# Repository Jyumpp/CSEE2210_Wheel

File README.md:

# CSEE2210_Wheel
## Rafferty Wong, Nick Piotrowski, Hunter Halloran

We made a wheelchair wheel with eddy-current braking

- Arduino code in `wheelSpeed.ino`
- Circuit schematic in `Wheel.sch`
- Circut board drawing in `Wheel.brd`
- Disk sketches in `image.png` and `image (1).png`
- Testing results in `csee graph.pdf`

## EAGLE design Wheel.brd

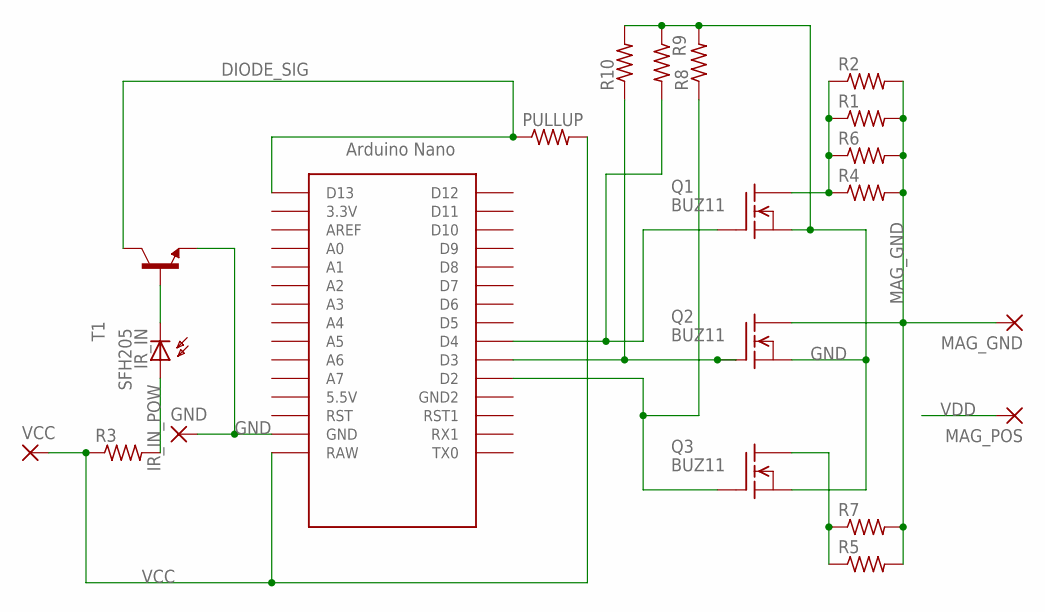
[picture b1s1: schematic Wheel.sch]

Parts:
GND: 3,81/1,4
IR_IN: SFH205
MAG_GND: 3,81/1,4
MAG_POS: 3,81/1,4
PULLUP: R-US_0204/7; 0204/7
Q1, Q2, Q3: BUZ11; TO220
R1, R2, R3, R4, R5, R6, R7, R8, R9, R10: R-US_0204/7; 0204/7
T1: -NPN-TO92-EBC; TO92-EBC
U$1: NANO
VCC: 3,81/1,4

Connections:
D2_SIG: Q3.1 (G), R8.1, U$1.D2
D3_SIG: Q2.1 (G), R10.1, U$1.D3
D4_SIG: Q1.1 (G), R9.2, U$1.D4
DIODE_SIG: PULLUP.1, T1.C, U$1.D13
DIODE_SIG_LOW: IR_IN.K (C), T1.B
GND: GND.1, Q1.3 (S), Q2.3 (S), Q3.3 (S), R8.2, R9.1, R10.2, T1.E, U$1.GND
IR_IN_POW: IR_IN.A, R3.2
LOW_SPEED_GND: Q1.2 (D), R1.1, R2.1, R4.1, R6.1
MAG_GND: MAG_GND.1, Q2.2 (D), R1.2, R2.2, R4.2, R5.2, R6.2, R7.2
MED_SPEED_GND: Q3.2 (D), R5.1, R7.1
VCC: PULLUP.2, R3.1, U$1.RAW, VCC.1
VDD: MAG_POS.1

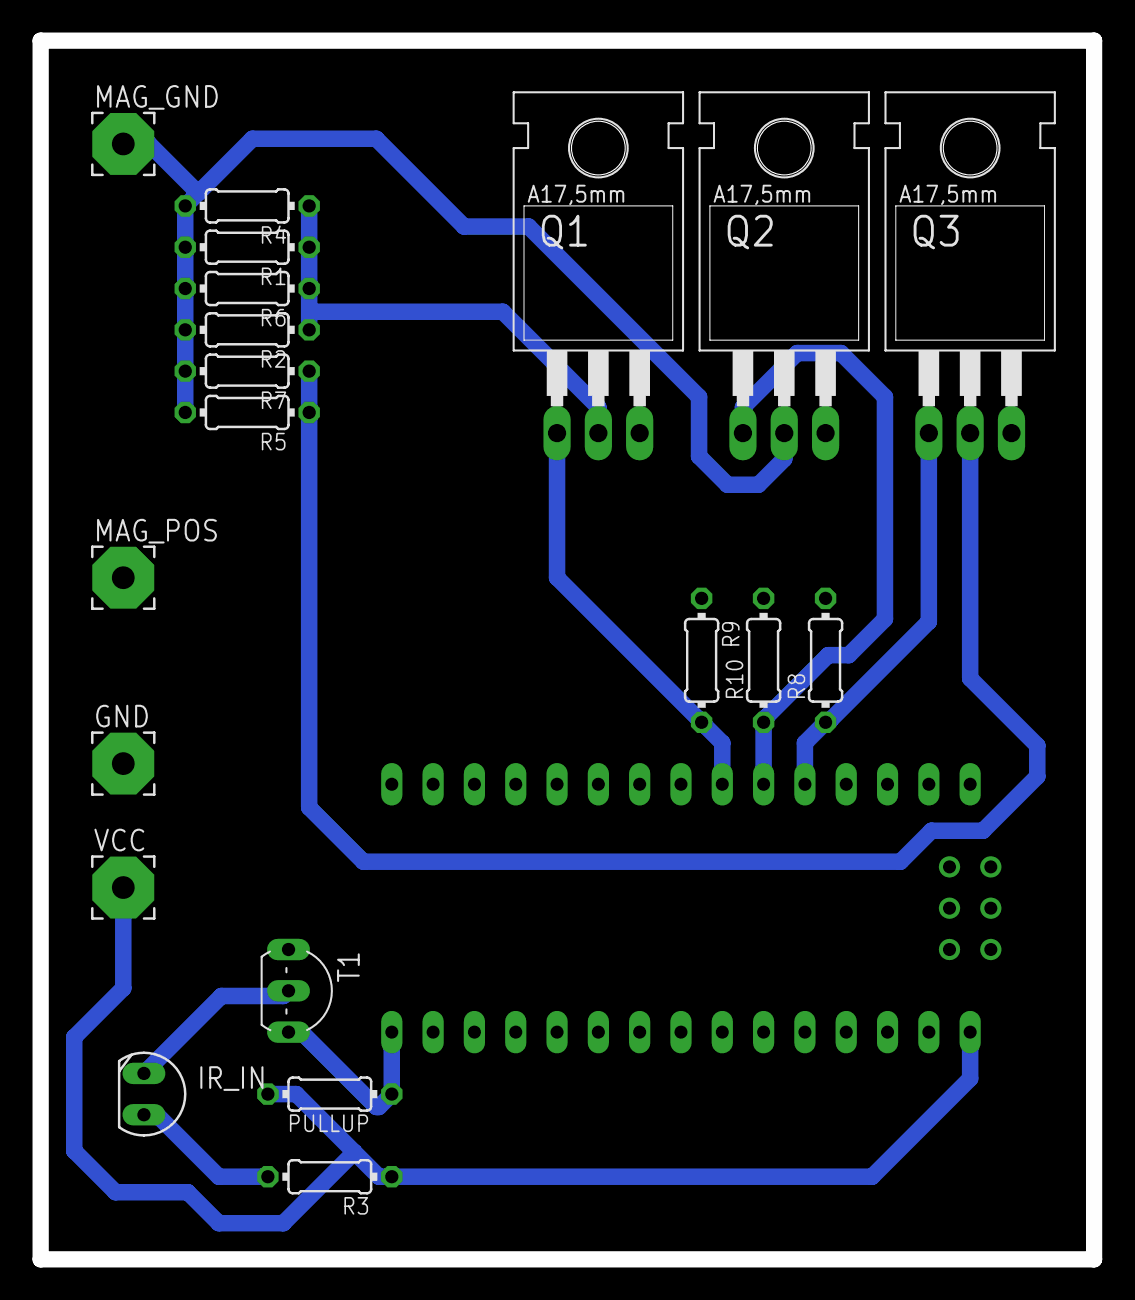
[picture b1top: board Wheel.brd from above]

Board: 2 copper layers, 64.8 x 74.9 mm, 21 parts (0 on the bottom side), 11 nets.
